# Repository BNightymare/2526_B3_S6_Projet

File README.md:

# 🤖 Projet Robot Suiveur de ligne
**Projet S6 · B3 · 2025–2026**

*Un robot autonome de type Segway capable de suivre une ligne au sol, conçu de A à Z : PCB, mécanique 3D et code Python.*

---
# 📅 Journal de bord

## 👥 Équipe

| Membre | Rôles principaux |
|--------|-----------------|
| **Clara** | Schéma KiCad LMS6DSOX, routage, Gerber), Structure 3D (Onshape), Tests fonctionnels, Code |
| **Lucie** | Schéma KiCad TMC2225, Soudure, routage, Code (IMU, moteurs, intégration) |
| **Samir** | Schéma KiCad MCP3208, Sertissage, Soudure, routage, Code (suiveur de ligne, intégration) |

<br>

## 🧩 Architecture matérielle
 
| Composant | Rôle | Datasheet |
|-----------|------|-----------|
| **Raspberry Pi Zero 2W** | Cerveau du robot. C'est lui qui donne les ordres aux composants via Python | [📄 Datasheet](https://www.raspberrypi.com/products/raspberry-pi-zero-2-w/) |
| **LSM6DSOX** | IMU — Gyroscope & accéléromètre (I²C) | [📄 Datasheet](https://github.com/user-attachments/files/24759821/Datasheet.LSM6DSOX.pdf) |
| **TMC2225** | Contrôle les moteurs pas à pas qui servent de roues au robot. | [📄 Datasheet](https://www.analog.com/media/en/technical-documentation/data-sheets/TMC2225_datasheet_rev1.14.pdf) |
| **MCP3208** | Interface entre les capteurs analogique et la Raspberry Pi. Permet de mesurer la distance des obstacles via les capteurs infrarouges sur les 8 canneaux. | [📄 Datasheet](https://ww1.microchip.com/downloads/en/DeviceDoc/21298E.pdf) |

<br>

## Structure du dépot github
📦 2526_B3_S6_Projet

 ┣ 1. PCB/    → Schémas KiCad, routage, fichiers Gerber
 
 ┣ 2. Code/   → Modules Python (IMU, moteurs, ligne)
 
 ┣ 3. 3D/     → Fichiers Onshape / STL
 
 ┗ 📄 README.md

<br>

<br>
<br>

---

# 20/01/2026 — Lancement du projet
> **Objectif :** Prise en main du projet pour définir les fonctionnalités du robot et les tâches à réaliser. 
> Cadrage, répartition des tâches et prise en main des composants.
 
**Tous :**
- Lecture des datasheets et extraction des caractéristiques électriques clés (tensions, courants, pinouts)
- Création du dépôt GitHub et mise en place de l'arborescence
- Rédaction du diagramme de Gantt (planification des étapes)
- Début des schémas KiCad individuels

<br>

---
# 20/01 - Initialisation
## Cahier des charges
> Prise en main du projet pour définir les fonctionnalités du robot et les tâches à réaliser.

Voici les principaux composants du robot:
| Composant | Rôle | Datasheet |
| :--- | :--- | :--- |
| Raspberry Pi 0 2W | Cerveau du robot. C'est lui qui donne les ordres aux composants via Python | [Datasheet Raspberry Pi 0 2W](https://www.raspberrypi.com/products/raspberry-pi-zero-2-w/) |
| LMS6DSOX | Gyroscope et accéléromètre | [Datasheet LMS6DSOX](https://github.com/user-attachments/files/24759821/Datasheet.LSM6DSOX.pdf) |
| TMC2225 | Contrôle les moteurs pas à pas qui servent de roues au robot. | [Datasheet TMC2225](https://www.analog.com/media/en/technical-documentation/data-sheets/TMC2225_datasheet_rev1.14.pdf) |
| MCP3208 | Interface entre les capteurs analogique et la Raspberry Pi. Permet de mesurer la distance des obstacles via les capteurs infrarouges sur les 8 canneaux. | [Datasheet MCP3208](https://ww1.microchip.com/downloads/en/DeviceDoc/21298E.pdf) |

## Github, diagramme de Gantt et attribution des tâches
**Github**
Création du dépot Github et mise en place de l'arborescence du projet.

**Diagramme de Gantt:**
Création d'un diagramme de Gant pour visualiser les étapes de conceptions du projet ainsi que la programmation dans le temps.

**Répartition des tâches:**
Le groupe s'est répartie l'étude des trois composants. Pour chaque composant, nous avons analysé la datasheet afin d'extraire les caractéristiques électriques (tensions, courants, pin...) nécessaire à la conception du schéma Kicad.

- Datasheet
- Début schéma KiCad 

---
# 21/01 - [1. PCB](https://github.com/BNightymare/2526_B3_S6_Projet/tree/1.-PCB) : Schéma Kicad 
> Concevoir les schémas électroniques de chaque composant.

- Clara : [Schéma du LMS6DSOX](https://github.com/BNightymare/2526_B3_S6_Projet/tree/1.-PCB/Projet%206%20KICAD%20LSM6DSOX)
- Lucie : [Schéma du TMC2225](https://github.com/BNightymare/2526_B3_S6_Projet/tree/1.-PCB/Projet%20S6) → [Correction TMC2225](https://github.com/BNightymare/2526_B3_S6_Projet/tree/1.-PCB/Projet%206%20KICAD%20TMC2225)
- Samir : [Schéma du MCP3208](https://github.com/BNightymare/2526_B3_S6_Projet/tree/1.-PCB/Projet6) → [Correction MCP3208](https://github.com/BNightymare/2526_B3_S6_Projet/tree/1.-PCB/Projet%206%20KICAD%20MCP3208)

**Correction des schémas KiCad par Mr. Fiack:**
- Raspberry à besoin d'une tension de 5V;
- Pour le TMC éviter de faire un copié-collé du schéma mais plutôt dupliquer la page, ce qui permet quand on fait les modifications sur une page de les voir sur la page dupliquer;
- Eviter les labels globaux et mettre des labels hiérarchique;
- Faire attention à ne pas relier un 3.3V du MOSFET à un 3.3V de la Raspberry, cela peut créer un court-circuit;
- Faire une page dans le schéma Kicad juste pour le Power_supply;
- Mettre des LEDS dans le schéma pour vérifier que le courant passe bien;
- Brancher une résistance aux LEDS pour éviter des les faire cramer.

Clara : [Schéma complet KiCad](https://github.com/BNightymare/2526_B3_S6_Projet/tree/1.-PCB/Projet%206%20KICAD%20CLS%20COMPLET)

---
# 23/01-26/01 - [1. PCB](https://github.com/BNightymare/2526_B3_S6_Projet/tree/1.-PCB) : Routage Kicad
> Routage du PCB, attribution des références MPN, génération des fichiers de fabrication.

- Clara : Routage du PCB Complet et attribution des MPN
- Lucie : Mise à jour de la documentation
- Samir et Lucie : Recherche des composants

---
# 17/02- 3. Intégration mécanique : 3D et soudure
> Concevoir, imprimer et assembler la structure physique du robot.
> Souder les composants et valider le PCB.

- Clara : Refaire et imprimer support 3D
- Samir et Lucie : Soudure des composants sur la carte

---
# 18/02:
- Samir et Lucie: Code (Nous avons réussi à faire fonctionner le TMC2225 et le MCP3208 mais nous rencontrons des problèmes avec les moteurs.)
- Samir: Sertissage
- Clara: 3D

---
# 19/02:
- Samir et Lucie: Code (Nous avons réussi à faire fonctionner le TMC2225 et le MCP3208 mais nous rencontrons des problèmes avec les moteurs.)
- Clara: 3D

---
# 20/02:
- Samir et Lucie: Code (Nous avons réussi à faire fonctionner le TMC2225 et le MCP3208 mais nous rencontrons des problèmes avec les moteurs.)
- Clara: 3D

---
# 17/03:
- Samir et Lucie: Code (Nous avons réussi à faire fonctionner le TMC2225 et le MCP3208 mais nous rencontrons des problèmes avec les moteurs.)
- Samir: Sertissage
- Clara: 3D

---
# 18/03:
- Samir et Lucie: Code
- Samir: Sertissage
- Clara: 3D 

---
# 19/03:
- Samir et Lucie: Code
- Samir: Sertissage
- Clara: 3D

---
# 20/03:
- Samir et Lucie: Code
- Samir: Sertissage
- Clara: 3D

Nous avions un problème de contact avec les batteries, ce qui causait notre problème avec les moteurs.

---
# 14/04:
- Lucie: Canva et Code
- Samir: Sertissage
- Clara : Code

---
# 15/04:
- Lucie: Code et Canva
- Samir: Sertissage
- Clara : Canva et code

---
# 17/04:
Soutenance finale

---
# Avancement global
| Etape | Avancée |
| :--- | :--- |
| PCB Design          | ████████████████████  100% ✅ |
| Mise en service     | ████████████████████  100% ✅ |
| Code Python         | ██████████░░░░░░░░░░   50% 🔄 |
| Intégration mécanique    | ████████████████████  100% ✅ |
| Validation finale   | ████████████████████  100% ✅ |

---

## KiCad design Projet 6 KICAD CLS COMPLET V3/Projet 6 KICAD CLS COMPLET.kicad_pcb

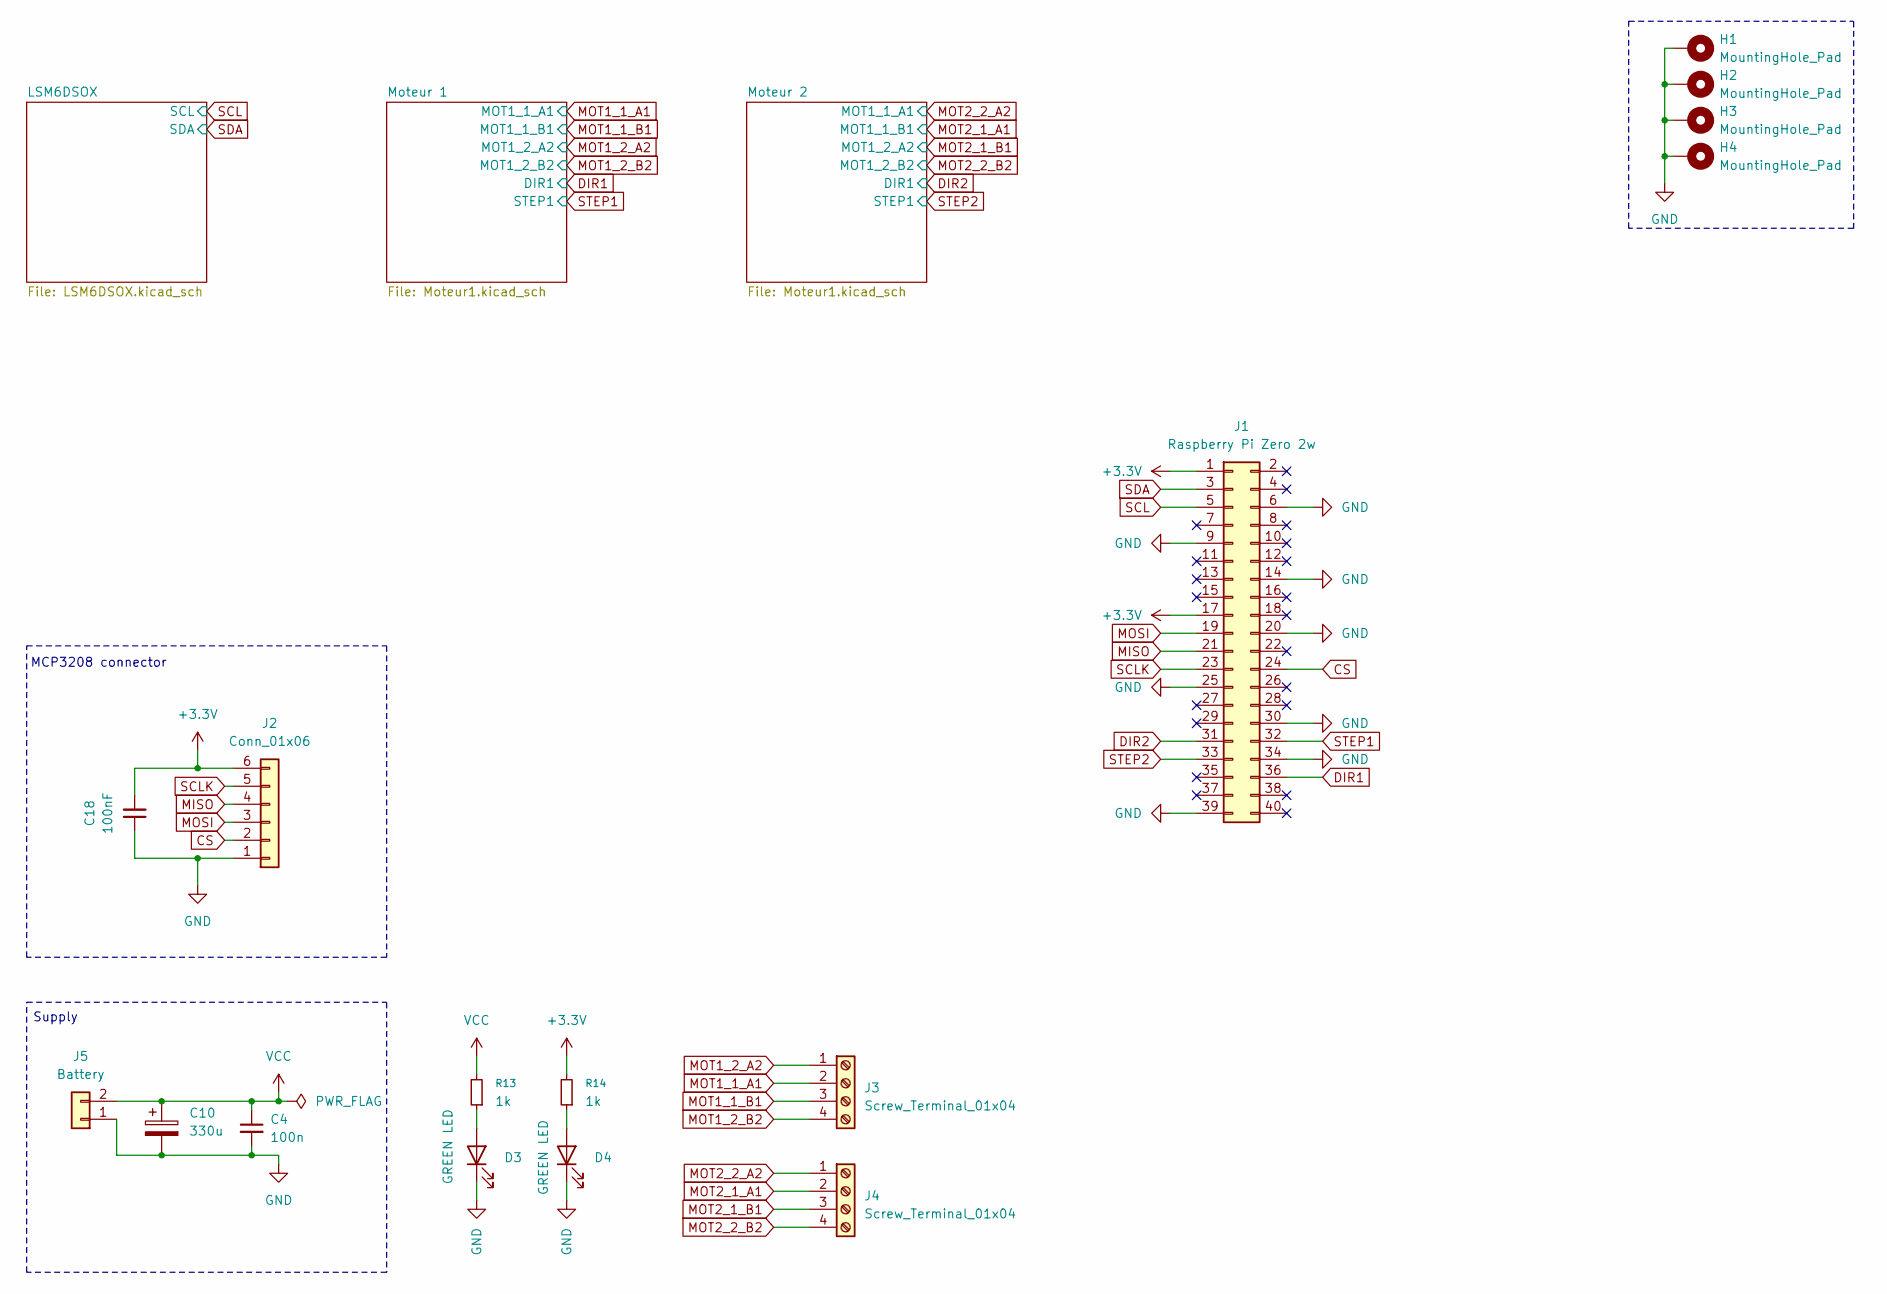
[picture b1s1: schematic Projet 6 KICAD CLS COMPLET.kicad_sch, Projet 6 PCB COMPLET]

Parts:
C4: 100n; C_0603_1608Metric; MPN 885012206071
C10: 330u; CP_Elec_6.3x5.4
C18: 100nF; C_0603_1608Metric; MPN 885012206071
D3, D4: GREEN LED; LED_0603_1608Metric; MPN 150060GS55040
H1, H2, H3, H4: MountingHole_Pad; MountingHole_2.7mm_M2.5_Pad
J1: Raspberry Pi Zero 2w; PinSocket_2x20_P2.54mm_Vertical
J2: Conn_01x06; JST_PH_B6B-PH-K_1x06_P2.00mm_Vertical
J3, J4: Screw_Terminal_01x04; JST_PH_B4B-PH-K_1x04_P2.00mm_Vertical
J5: Battery; JST_EH_B2B-EH-A_1x02_P2.50mm_Vertical
R13, R14: 1k; R_0603_1608Metric

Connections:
+3.3V: C18.2, J1.1, J1.17, J2.6, R14.2; also elsewhere on the board
CS: J1.24, J2.2
DIR1: J1.36; also elsewhere on the board
DIR2: J1.31; also elsewhere on the board
GND: C4.2, C10.2, C18.1, D3.1 (K), D4.1 (K), H1.1, H2.1, H3.1, H4.1, J1.6, J1.9, J1.14, J1.20, J1.25, J1.30, J1.34, J1.39, J2.1, J5.1; also elsewhere on the board
MISO: J1.21, J2.4
MOSI: J1.19, J2.3
MOT1_1_A1: J3.2; also elsewhere on the board
MOT1_1_B1: J3.3; also elsewhere on the board
MOT1_2_A2: J3.1; also elsewhere on the board
MOT1_2_B2: J3.4; also elsewhere on the board
MOT2_1_A1: J4.2; also elsewhere on the board
MOT2_1_B1: J4.3; also elsewhere on the board
MOT2_2_A2: J4.1; also elsewhere on the board
MOT2_2_B2: J4.4; also elsewhere on the board
unnamed: D3.2 (A), R13.1
unnamed: D4.2 (A), R14.1
SCL: J1.5; also elsewhere on the board
SCLK: J1.23, J2.5
SDA: J1.3; also elsewhere on the board
STEP1: J1.32; also elsewhere on the board
STEP2: J1.33; also elsewhere on the board
VCC: C4.1, C10.1, J5.2, R13.2; also elsewhere on the board

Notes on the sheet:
MCP3208 connector
Supply

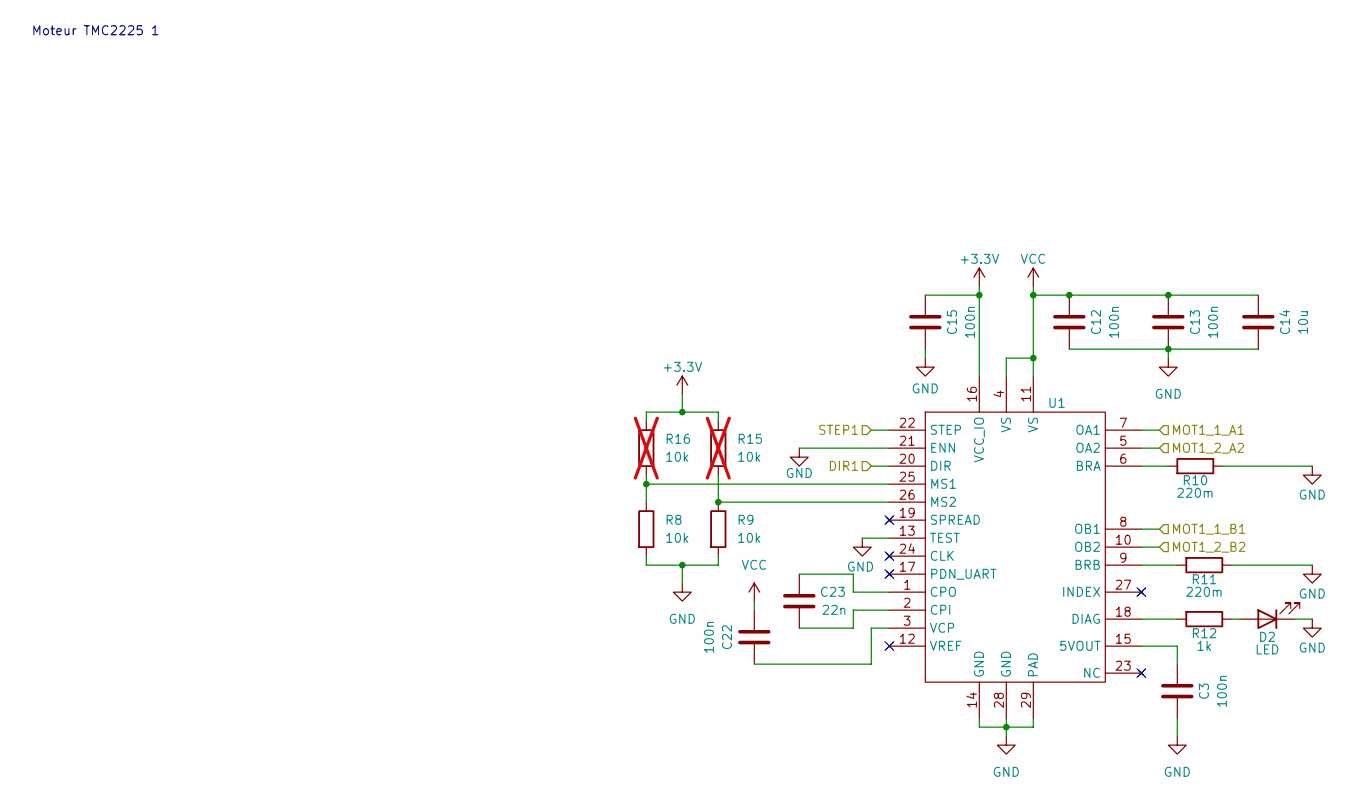
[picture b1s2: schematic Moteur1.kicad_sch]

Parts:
C3, C12, C13, C15, C22: 100n; C_0805_2012Metric
C14: 10u; C_0805_2012Metric
C23: 22n; C_0805_2012Metric
D2: LED; LED_0603_1608Metric
R8, R9: 10k; R_0603_1608Metric
R10, R11: 220m; R_1206_3216Metric
R12: 1k; R_0603_1608Metric
R15, R16: 10k; R_0603_1608Metric; not fitted
U1: HTSSOP-28-1EP_4.4x9.7mm_P0.65mm_EP2.85x5.4mm_ThermalVias

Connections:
+3.3V: C15.1, R15.1, R16.1, U1.16 (VCC_IO); also elsewhere on the board
DIR1: U1.20 (DIR); also elsewhere on the board
GND: C3.2, C12.2, C13.2, C14.2, C15.2, D2.1 (K), R8.2, R9.2, R10.1, R11.1, U1.13 (TEST), U1.14 (GND), U1.21 (ENN), U1.28 (GND), U1.29 (PAD); also elsewhere on the board
MOT1_1_A1: U1.7 (OA1); also elsewhere on the board
MOT1_1_B1: U1.8 (OB1); also elsewhere on the board
MOT1_2_A2: U1.5 (OA2); also elsewhere on the board
MOT1_2_B2: U1.10 (OB2); also elsewhere on the board
unnamed: D2.2 (A), R12.1
unnamed: C3.1, U1.15 (5VOUT)
unnamed: R10.2, U1.6 (BRA)
unnamed: R11.2, U1.9 (BRB)
unnamed: C23.2, U1.2 (CPI)
unnamed: C23.1, U1.1 (CPO)
unnamed: R12.2, U1.18 (DIAG)
unnamed: R8.1, R16.2, U1.25 (MS1)
unnamed: R9.1, R15.2, U1.26 (MS2)
unnamed: C22.1, U1.3 (VCP)
STEP1: U1.22 (STEP); also elsewhere on the board
VCC: C12.1, C13.1, C14.1, C22.2, U1.4 (VS), U1.11 (VS); also elsewhere on the board

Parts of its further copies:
C5, C7, C8, C9: 100n; C_0805_2012Metric
C6: 22n; C_0805_2012Metric
C16: 10u; C_0805_2012Metric
D1: LED; LED_0603_1608Metric
R1, R3: 10k; R_0603_1608Metric; not fitted
R2, R7: 10k; R_0603_1608Metric
R17, R18: 220m; R_1206_3216Metric
R19: 1k; R_0603_1608Metric
U2: HTSSOP-28-1EP_4.4x9.7mm_P0.65mm_EP2.85x5.4mm_ThermalVias

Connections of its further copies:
+3.3V: C7.1, R1.1, R3.1, U2.16 (VCC_IO); also elsewhere on the board
DIR2: U2.20 (DIR); also elsewhere on the board
GND: C7.2, C8.2, C9.2, C16.2, D1.1 (K), R2.2, R7.2, R17.1, R18.1, U2.13 (TEST), U2.14 (GND), U2.21 (ENN), U2.28 (GND), U2.29 (PAD); also elsewhere on the board
MOT2_1_A1: U2.8 (OB1); also elsewhere on the board
MOT2_1_B1: U2.5 (OA2); also elsewhere on the board
MOT2_2_A2: U2.7 (OA1); also elsewhere on the board
MOT2_2_B2: U2.10 (OB2); also elsewhere on the board
unnamed: D1.2 (A), R19.1
unnamed 28: U2.15 (5VOUT); also elsewhere on the board
unnamed: R17.2, U2.6 (BRA)
unnamed: R18.2, U2.9 (BRB)
unnamed: C6.2, U2.2 (CPI)
unnamed: C6.1, U2.1 (CPO)
unnamed: R19.2, U2.18 (DIAG)
unnamed: R1.2, R2.1, U2.25 (MS1)
unnamed: R3.2, R7.1, U2.26 (MS2)
unnamed: C5.1, U2.3 (VCP)
STEP2: U2.22 (STEP); also elsewhere on the board
VCC: C5.2, C8.1, C9.1, C16.1, U2.4 (VS), U2.11 (VS); also elsewhere on the board

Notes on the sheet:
Moteur TMC2225 1

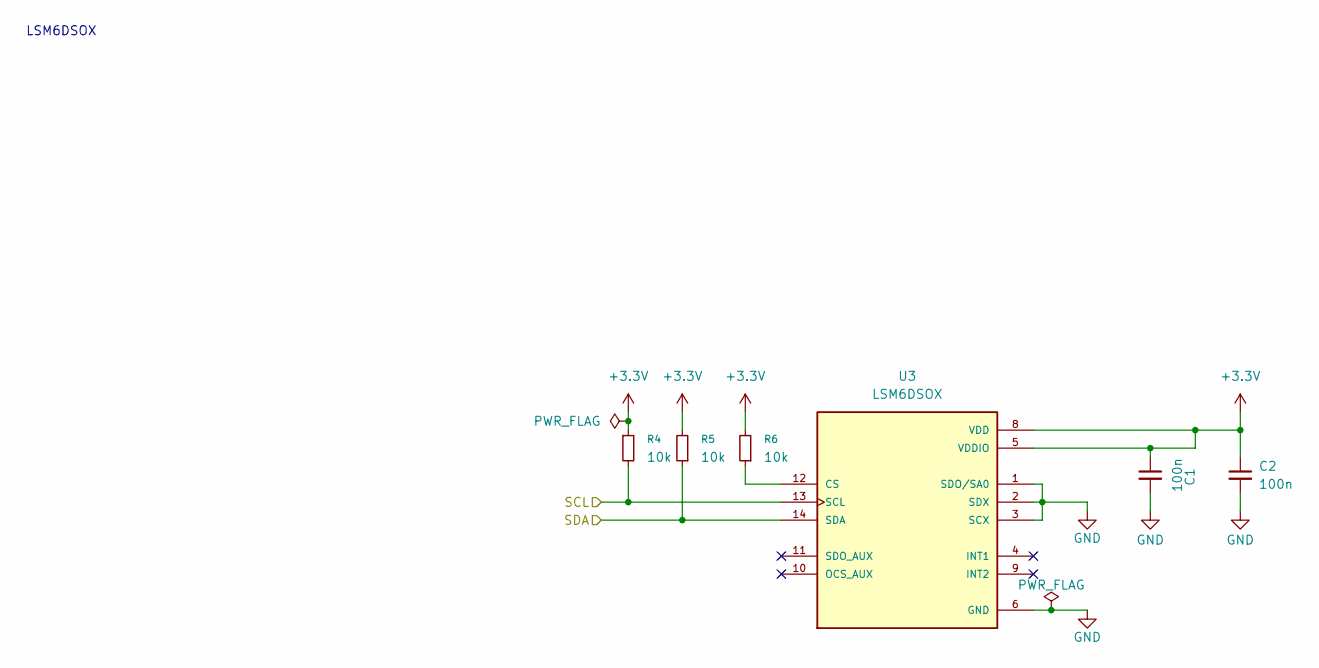
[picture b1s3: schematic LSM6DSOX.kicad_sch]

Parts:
C1, C2: 100n; C_0603_1608Metric; MPN 885012206071
R4, R5, R6: 10k; R_0603_1608Metric
U3: LSM6DSOX; PQFN50P250X300X86-14N; PARTREV 3.0

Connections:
+3.3V: C1.1, C2.1, R4.1, R5.2, R6.2, U3.5 (VDDIO), U3.8 (VDD); also elsewhere on the board
GND: C1.2, C2.2, U3.1 (SDO/SA0), U3.2 (SDX), U3.3 (SCX), U3.6 (GND), U3.7 (GND); also elsewhere on the board
unnamed: R6.1, U3.12 (CS)
SCL: R4.2, U3.13 (SCL); also elsewhere on the board
SDA: R5.1, U3.14 (SDA); also elsewhere on the board

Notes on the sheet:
LSM6DSOX

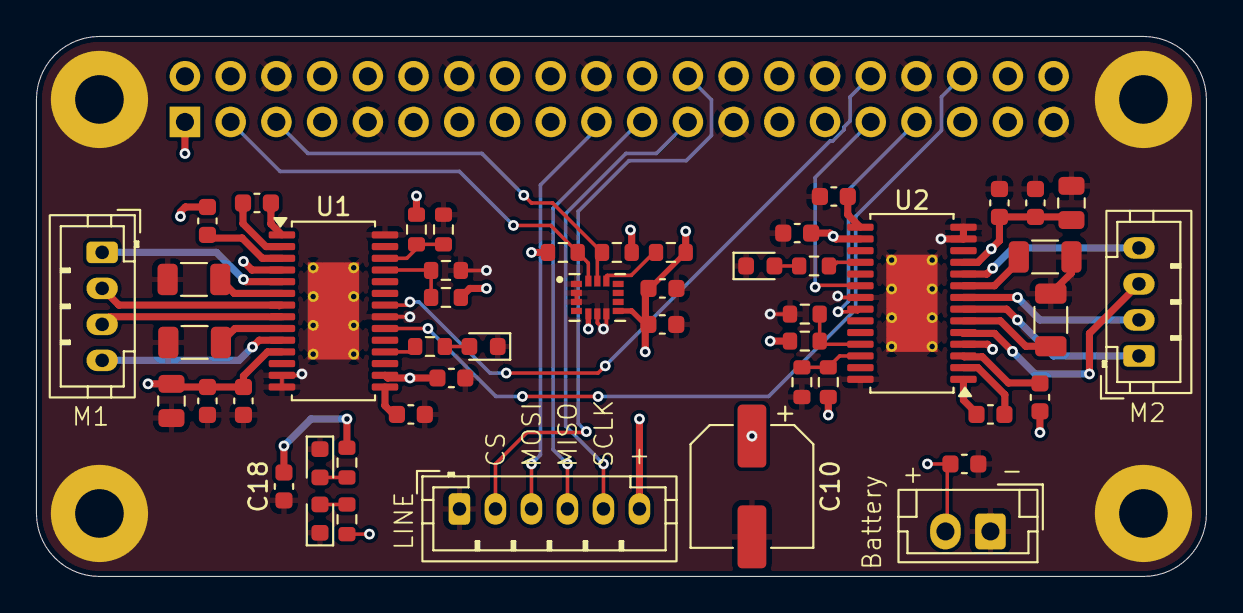
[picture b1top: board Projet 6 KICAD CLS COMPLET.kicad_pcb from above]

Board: 4 copper layers, 65.0 x 30.0 mm, 54 parts (1 on the bottom side), 44 nets.

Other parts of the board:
C11: 2u2; C_0603_1608Metric

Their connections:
GND: C11.2; also elsewhere on the board
unnamed 28: C11.1; also elsewhere on the board

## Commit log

2026-01-20 Initial plan
2026-01-20 Add PCB project structure and documentation
2026-01-20 Add Python project structure with source, tests, and configuration
2026-01-20 Fix setup.py package discovery and simplify test implementation
2026-01-20 Implement core asservi module with PID controller and motor control
2026-01-20 Fix hardcoded paths in example scripts for portability
2026-01-20 Add signal filtering module with filters and documentation
2026-01-20 Add .gitignore and remove Python bytecode files
2026-01-20 Optimize MovingAverageFilter using deque for O(1) operations
2026-01-20 Integrate all project modules for final submission
2026-01-20 Add complete Express.js routing system with RESTful API
2026-01-20 Add LICENSE and CONTRIBUTING files
2026-01-20 Add comprehensive system architecture schema documentation
2026-01-20 Address code review feedback
2026-01-20 Fix require paths in routes/index.js
2026-01-20 Add input validation for product creation and update operations
2026-01-20 Add mechanical integration structure and documentation
2026-01-20 Add M5 and M8 fastener clearances to guidelines
2026-01-20 Add PCB commissioning documentation and testing scripts
2026-01-20 Refactor bilingual prompts to reduce code duplication
2026-01-21 Projet 6 TMC2225
2026-01-21 Update README with project details and task assignments
2026-01-21 Add files via upload
    Schéma du MCP3208 corrigé
2026-01-21 Add files via upload
    Schéma du TMC2225 corrigé
2026-01-21 Add files via upload
    Schéma PCB COMPLET
2026-01-21 Revise README for PCB project details
    Updated the README to include detailed PCB project information, including component datasheets, schematics, and routing.
2026-01-21 Add PCB README with planning and tasks
    Added PCB project details including components, schematics, and routing.
2026-01-21 Add README with planning and tasks
2026-01-23 Update README with datasheet links
    Added datasheets for LMS6DSOX, TMC2225, and MCP3208.
2026-01-23 Projet 6 KICAD CLS COMPLET Correction
2026-01-23 Fix formatting and spacing in README.md
2026-01-23 Add files via upload
    Projet 6 KICAD CLS COMPLET Corrigé
2026-01-23 Revise README with project initialization and tasks
    Updated the README to include initialization details and project management tasks.
2026-01-23 Enhance README with component table and project info
    Added a table for components and updated project details.
2026-01-23 Update README with additional components and details
    Added TMC2225 and MCP3208 components with their roles and datasheets.
2026-01-23 Refine README formatting and project management section
    Updated formatting for section headers and clarified project management details.
2026-01-24 Revise README with new components and project details
    Updated the README to include new components and their datasheets, improved formatting, and clarified project tasks and responsibilities.
2026-01-25 Add files via upload
    PCB KICAD CLS COMPLET Routage
2026-01-26 Revise project initialization and KiCad corrections
    Updated project initialization details and added corrections for KiCad schematics.
2026-01-26 Modify PCB routing section in README
    Updated date range and added contributors to PCB routing section.
2026-01-26 Update date header and clarify PCB routing details
2026-01-26 Update README with component research details
2026-01-26 Fix formatting in README for PCB routing section
2026-01-26 Update README with datasheets and routing info
    Added datasheet links and updated routing section with date.
2026-01-26 Fix formatting and headings in README.md
    Corrected formatting and capitalization in the README.
2026-01-30 Update README with project title and badges
    Added project title and badges for KiCad, Raspberry Pi, and Python.
2026-02-18 Update README with new PCB soldering entry
2026-02-18 Update project progress and section headings
2026-03-17 Revise mechanical integration section in README
    Updated the mechanical integration section with clearer tasks.
2026-03-17 Fix formatting in date header of README
2026-03-17 Add new tasks for March in README
2026-03-18 mise à jour
2026-03-18 Refactor README for clarity and structure
    Updated the README to improve formatting and add progress indicators.
2026-03-18 Initialize README with project details and tasks
    Added project overview, components, and task distribution.
2026-03-18 Refactor motor driver to use gpiozero library
2026-03-18 Import RPI.GPIO and adjust driver.py structure
2026-03-18 Fix import statements and formatting in driver.py
2026-03-18 Refactor imports and maintain motor control logic
2026-03-18 Fix import statements and GPIO cleanup method
2026-03-18 Update team roles and progress notes in README
    Added 'Code' to Clara's role and updated progress notes.
2026-03-20 Revise project update for Samir and Lucie
    Updated project status for Samir and Lucie with details on TMC2225 and MCP3208 functionality issues.
2026-03-20 Update import paths for MCP3208 and line_detector
2026-04-15 Remove global advancement section from README
    Removed the global progress section from the README.
2026-04-15 Update roles for Samir in README
    Updated Samir's roles to include 'Sertissage' in the README.
2026-04-15 Update tasks for Samir and Lucie in README
    Added 'Sertissage' task for Samir and updated code tasks.
2026-04-15 Update README with progress reports for February and April
    Added progress updates for February and April, detailing tasks done by Samir, Lucie, and Clara.
2026-04-15 Comment out PID import in main.py
    Comment out the import statement for PID.
2026-04-15 Update README with project contributions details
2026-04-15 Reduce MAX_SPEED_RPM from 60.0 to 40.0
2026-04-16 Update roles for Lucie and Samir in README
2026-04-18 Revise contributions for 14/04 and 15/04
    Updated contributions for 14/04 and 15/04 to reflect changes in tasks.
